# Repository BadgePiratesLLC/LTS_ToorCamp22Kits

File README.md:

# LTS_ToorCamp22Kits
Kits we passed out at Toor Camp 2022

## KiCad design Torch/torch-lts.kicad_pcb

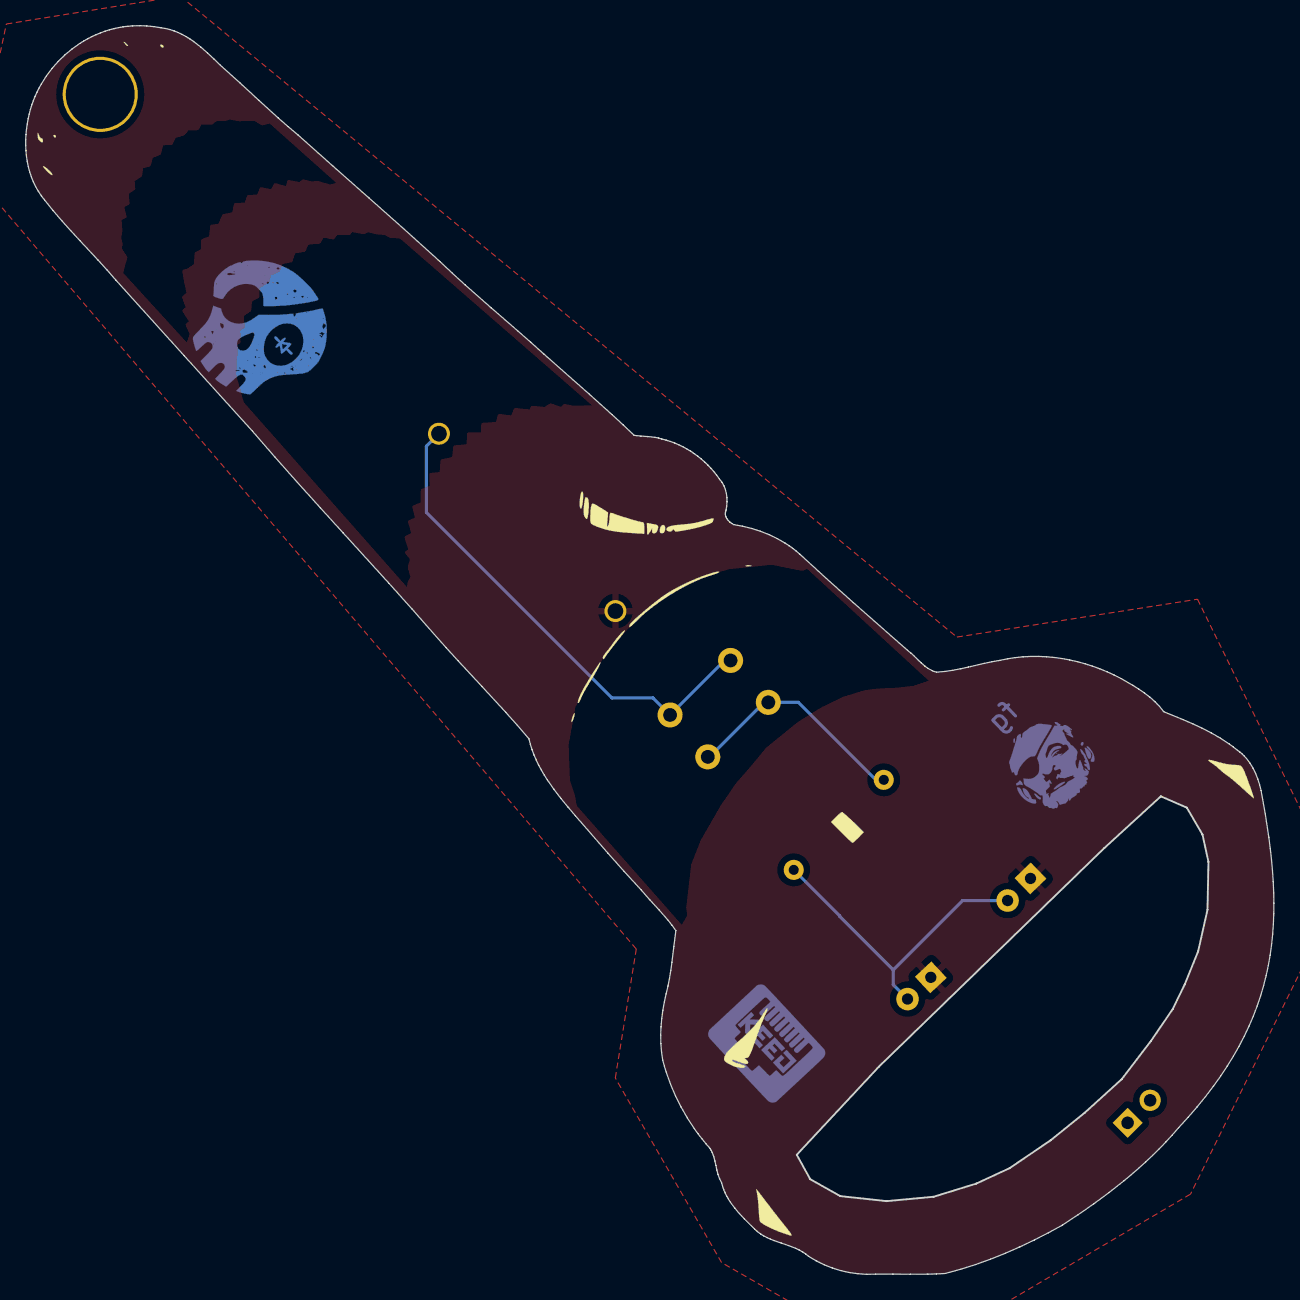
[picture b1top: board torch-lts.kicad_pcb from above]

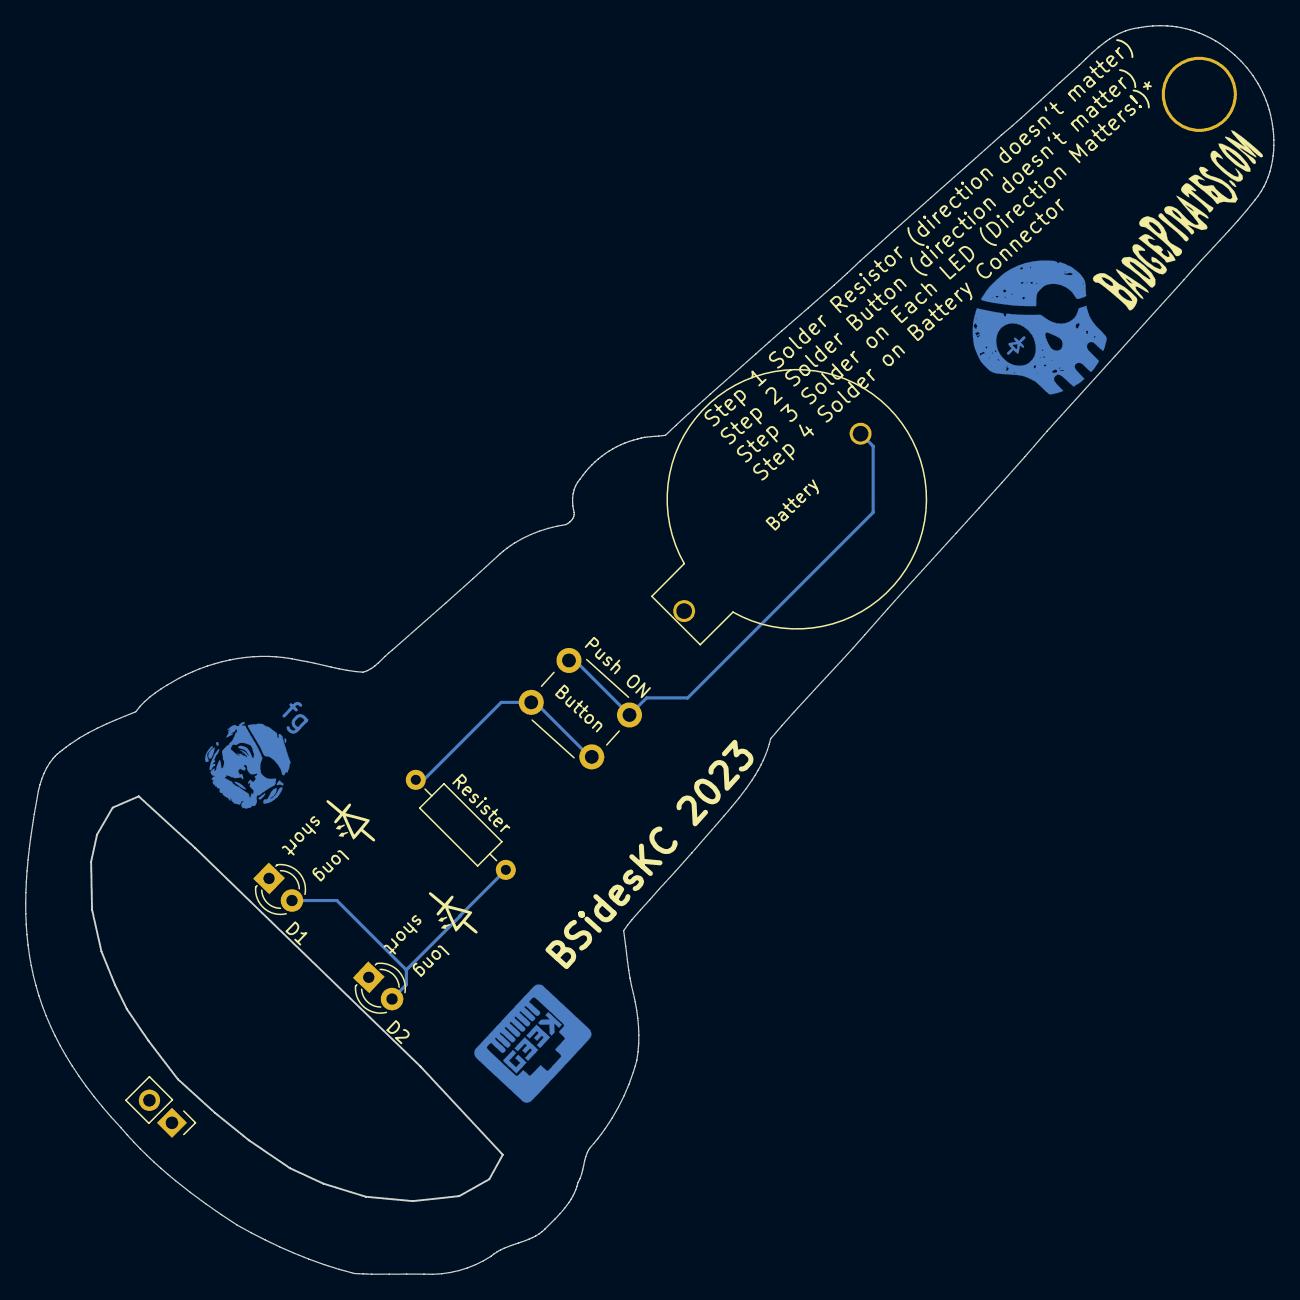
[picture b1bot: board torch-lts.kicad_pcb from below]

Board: 2 copper layers, 99.6 x 99.6 mm, 5 parts (5 on the bottom side), 4 nets.

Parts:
BT1: Battery; 2032 Through Hold Holder
Button: Push ON; SW_PUSH_6mm_H5mm
D1, D2: LED; LED_D3.0mm
Resister: R_US; R_Axial_DIN0207_L6.3mm_D2.5mm_P10.16mm_Horizontal

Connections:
GND: BT1.2 (-), D1.1 (K), D2.1 (K)
unnamed: BT1.1 (+), Button.1 (C)
unnamed: Button.2 (D), Resister.1
VCC: D1.2 (A), D2.2 (A), Resister.2

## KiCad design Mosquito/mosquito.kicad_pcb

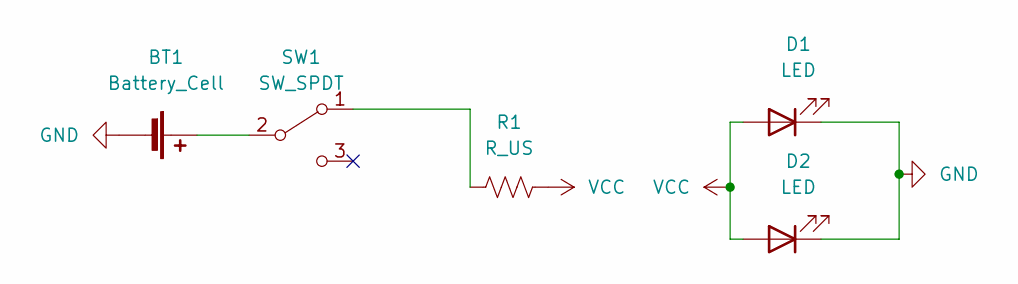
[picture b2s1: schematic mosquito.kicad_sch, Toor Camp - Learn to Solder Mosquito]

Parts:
BT1: Battery_Cell; BatteryHolder_MPD_BC2003_1x2032_Fixed
D1, D2: LED; LED_D3.0mm
R1: R_US; R_Axial_DIN0204_L3.6mm_D1.6mm_P5.08mm_Horizontal
SW1: SW_SPDT; SW_Slide_1P2T_CK_TH

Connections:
GND: BT1.2 (-), D1.1 (K), D2.1 (K)
unnamed: BT1.1 (+), SW1.2 (B)
unnamed: R1.1, SW1.1 (A)
VCC: D1.2 (A), D2.2 (A), R1.2

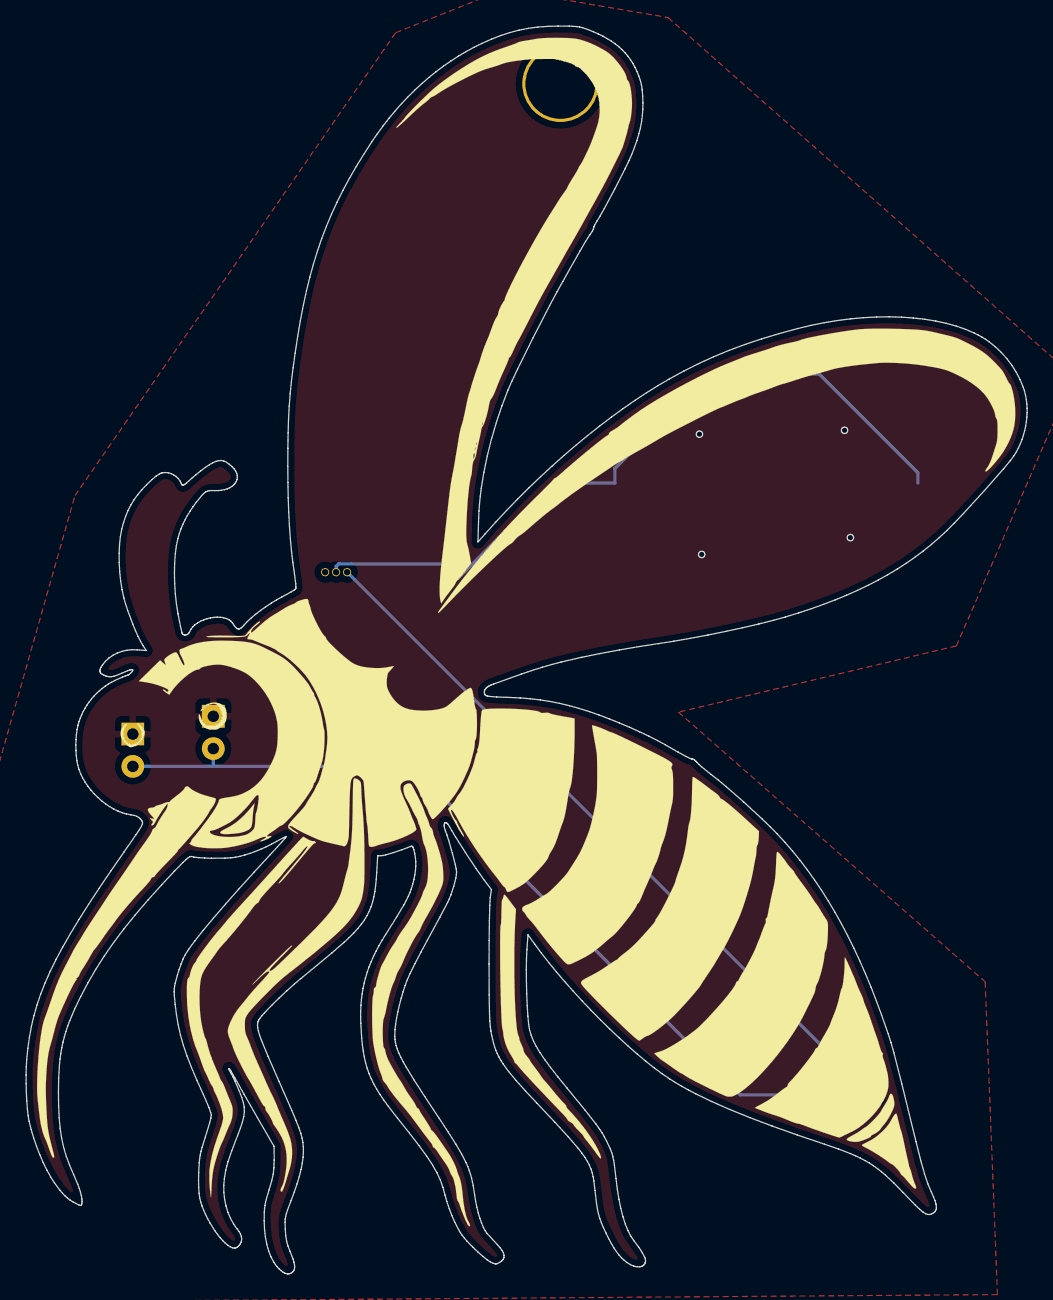
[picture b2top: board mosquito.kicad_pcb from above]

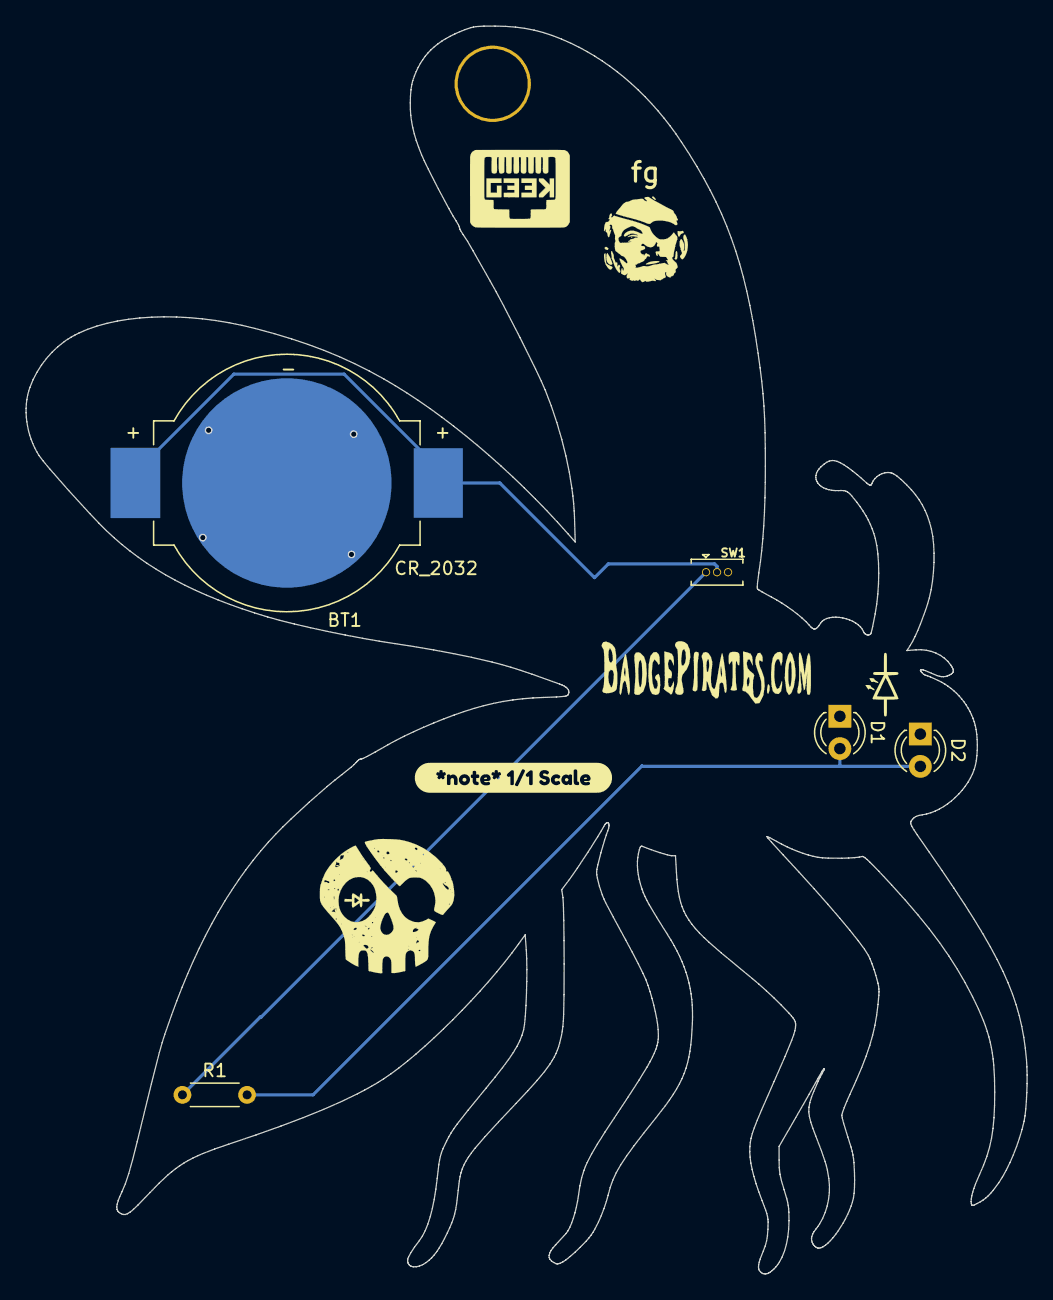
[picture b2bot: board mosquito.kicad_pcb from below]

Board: 2 copper layers, 78.7 x 98.1 mm, 6 parts (6 on the bottom side), 4 nets.

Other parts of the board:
kibuzzard-62B665C3: G***; kibuzzard-62B665C3

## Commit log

2022-10-17 pics updates
2022-10-18 Create file
2023-05-29 update for BSidesKC
2023-06-13 zips
2023-06-24 updated Logos and Adjusted size of res, alighted footprints properly to board
